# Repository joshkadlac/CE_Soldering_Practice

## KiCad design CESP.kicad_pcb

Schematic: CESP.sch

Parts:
BT1: BATTERY
C1: 100uF; Digikey 399-6102-ND
C2: 100uF; digikey 399-6102-ND
D1, D2: LED
Q1, Q2: NPN
R1, R4: 470
R2, R3: 10k

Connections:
unnamed: C2.1, D2.2 (K), Q2.3 (C)
unnamed: C1.2, Q2.2 (B), R3.2
unnamed: C1.1, D1.2 (K), Q1.3 (C)
unnamed: BT1.2 (-), Q1.1 (E), Q2.1 (E)
unnamed: D1.1 (A), R1.2
unnamed: D2.1 (A), R4.2
unnamed: C2.2, Q1.2 (B), R2.2
unnamed: BT1.1 (+), R1.1, R2.1, R3.1, R4.1

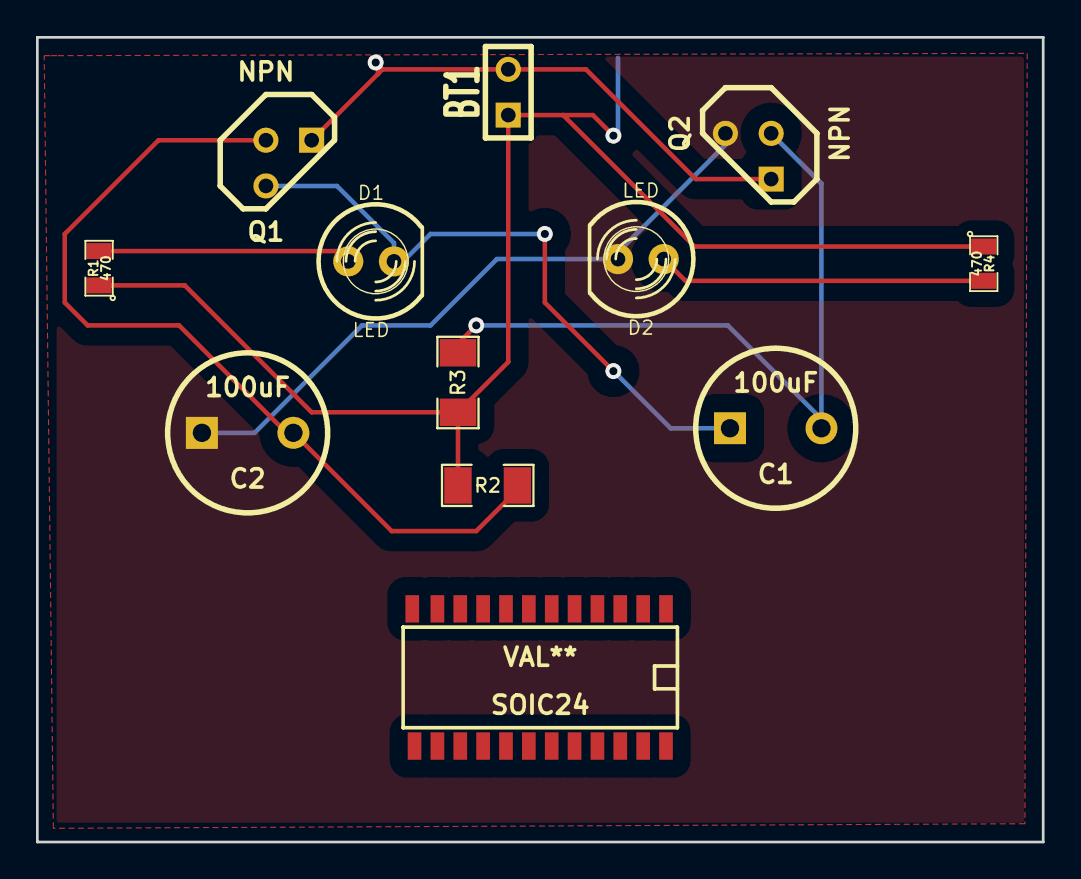
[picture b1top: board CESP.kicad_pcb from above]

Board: 2 copper layers, 55.9 x 44.7 mm, 12 parts (0 on the bottom side), 8 nets.

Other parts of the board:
SOIC24: VAL**; SOIC24

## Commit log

2014-01-27 Version1 commit
